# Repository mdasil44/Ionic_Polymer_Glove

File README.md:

# Ionic Polymer Glove

This repo contains the files used for testing and analyzing the performance of the sensorized glove using ionic polymer sensors.
The GUI is under sensorized-glove/Code/GUI/Matlab/IonicPolymerGloveGUI.mlapp

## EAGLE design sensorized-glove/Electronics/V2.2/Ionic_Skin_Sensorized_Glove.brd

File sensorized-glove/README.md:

# README #

### Summary ###

This repository contains all the relevant files for the ionic polymer sensorized glove project.

### Installation ###

- Matlab (See information engineering IT website)
- USB to bluetooth driver (See README.md in Code/Firmware/Bluetooth USB driver directory

### Contact ###

Developed by Andrew Cullen [acullen5@uwo.ca]

Supervised by Aaron Price [aaron.price@uwo.ca] and Ana Luisa Trejos [atrejos@uwo.ca]

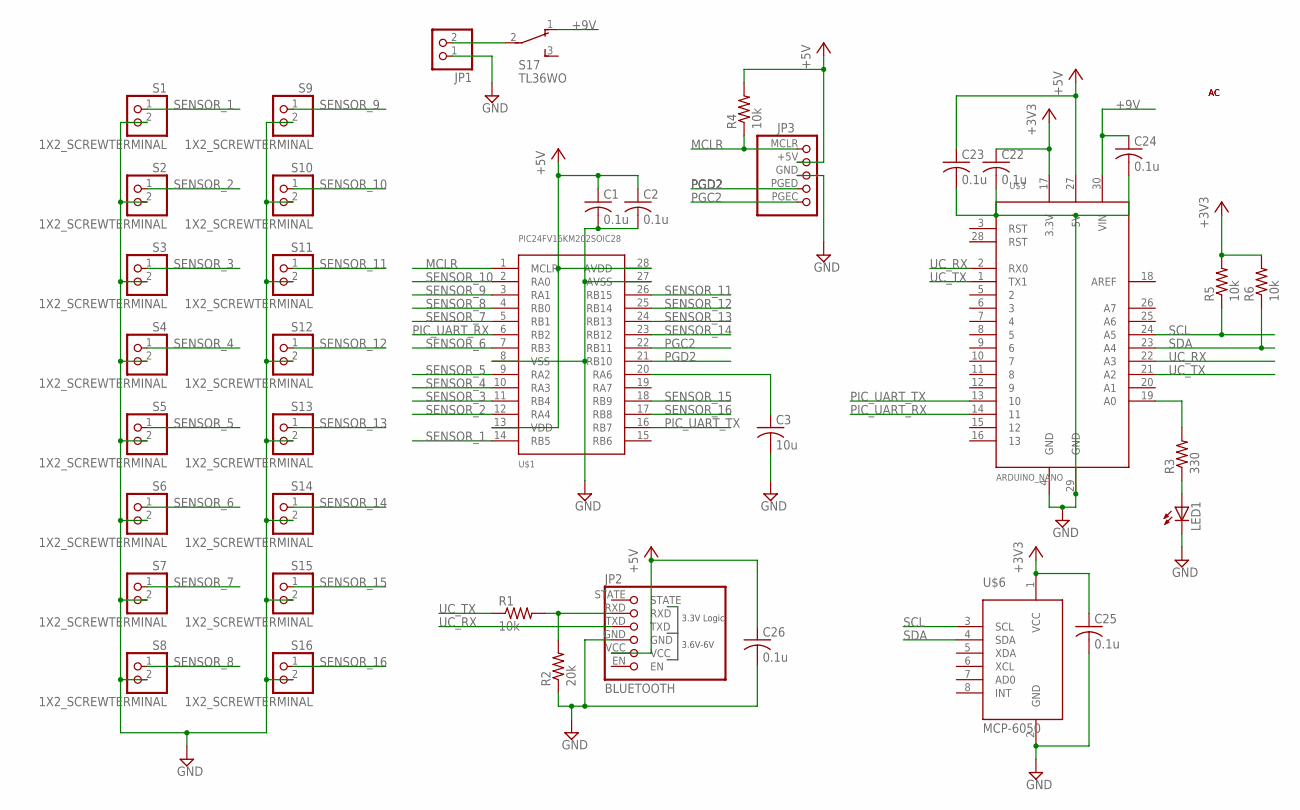
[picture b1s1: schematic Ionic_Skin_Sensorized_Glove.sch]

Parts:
C1, C2, C22, C23, C24, C25, C26: 0.1u; C0805
C3: 10u; C0805
JP1: PINHD-1X2; 1X02
JP2: BLUETOOTH; HC-06
JP3: PICKIT/90
LED1: LEDCHIPLED_0805; CHIPLED_0805
R1, R4, R5, R6: 10k; R0805
R2: 20k; R0805
R3: 330; R0805
S1, S2, S3, S4, S5, S6, S7, S8, S9, S10, S11, S12, S13, S14, S15, S16: 1X2_SCREWTERMINAL; 1X2-2.54MM
S17: TL36WO; TL3XWO
U$1: PIC24FV16KM202SOIC28; SOIC28
U$3: ARDUINO_NANO
U$6: MCP-6050; MCP-6050_BREAKOUT
U$7: AC_TOP
U$8: AC_BOTTOM

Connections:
+3V3: C22.1, C25.1, R5.2, R6.2, U$3.17 (3.3V), U$6.1 (VCC)
+5V: C1.1, C2.1, C23.1, C26.1, JP2.VCC, JP3.+5V (2), R4.2, U$1.13 (VDD), U$1.28 (AVDD), U$3.27 (5V)
+9V: C24.1, S17.1 (O), U$3.30 (VIN)
GND: C1.2, C2.2, C3.2, C22.2, C23.2, C24.2, C25.2, C26.2, JP1.1, JP2.GND, JP3.GND (3), LED1.C, R2.1, S1.2, S2.2, S3.2, S4.2, S5.2, S6.2, S7.2, S8.2, S9.2, S10.2, S11.2, S12.2, S13.2, S14.2, S15.2, S16.2, U$1.8 (VSS), U$1.27 (AVSS), U$3.4 (GND), U$3.29 (GND), U$6.2 (GND)
MCLR: JP3.MCLR (1), R4.1, U$1.1 (MCLR)
unnamed: C3.1, U$1.20 (RA6)
unnamed: JP1.2, S17.2
unnamed: LED1.A, R3.1
unnamed: R3.2, U$3.19 (A0)
unnamed: JP2.RXD, R1.2, R2.2
PGC2: JP3.PGEC (5), U$1.22 (RB11)
PGD2: JP3.PGED (4), U$1.21 (RB10)
PIC_UART_RX: U$1.6 (RB2), U$3.14 (11)
PIC_UART_TX: U$1.16 (RB7), U$3.13 (10)
SCL: R5.1, U$3.24 (A5), U$6.3 (SCL)
SDA: R6.1, U$3.23 (A4), U$6.4 (SDA)
SENSOR_1: S1.1, U$1.14 (RB5)
SENSOR_2: S2.1, U$1.12 (RA4)
SENSOR_3: S3.1, U$1.11 (RB4)
SENSOR_4: S4.1, U$1.10 (RA3)
SENSOR_5: S5.1, U$1.9 (RA2)
SENSOR_6: S6.1, U$1.7 (RB3)
SENSOR_7: S7.1, U$1.5 (RB1)
SENSOR_8: S8.1, U$1.4 (RB0)
SENSOR_9: S9.1, U$1.3 (RA1)
SENSOR_10: S10.1, U$1.2 (RA0)
SENSOR_11: S11.1, U$1.26 (RB15)
SENSOR_12: S12.1, U$1.25 (RB14)
SENSOR_13: S13.1, U$1.24 (RB13)
SENSOR_14: S14.1, U$1.23 (RB12)
SENSOR_15: S15.1, U$1.18 (RB9)
SENSOR_16: S16.1, U$1.17 (RB8)
UC_RX: JP2.TXD, U$3.2 (RX0), U$3.22 (A3)
UC_TX: R1.1, U$3.1 (TX1), U$3.21 (A2)

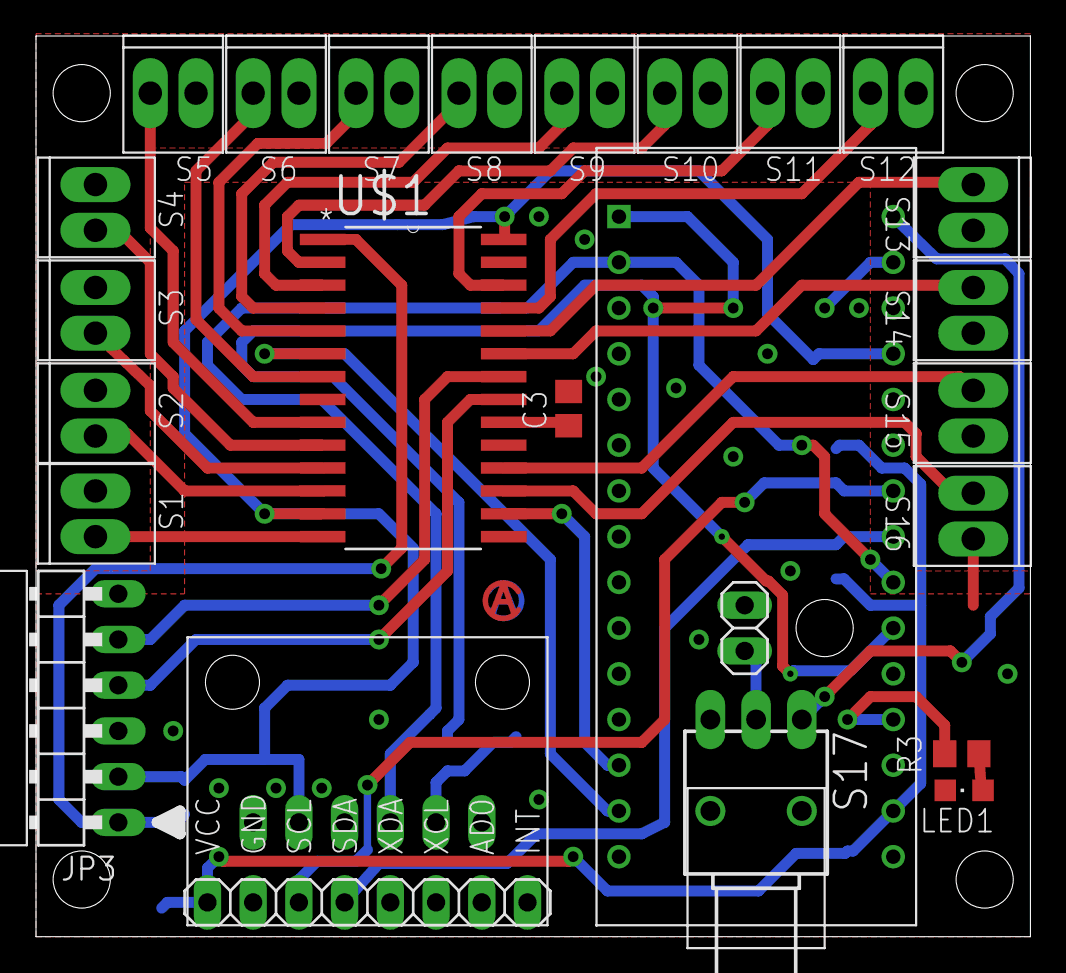
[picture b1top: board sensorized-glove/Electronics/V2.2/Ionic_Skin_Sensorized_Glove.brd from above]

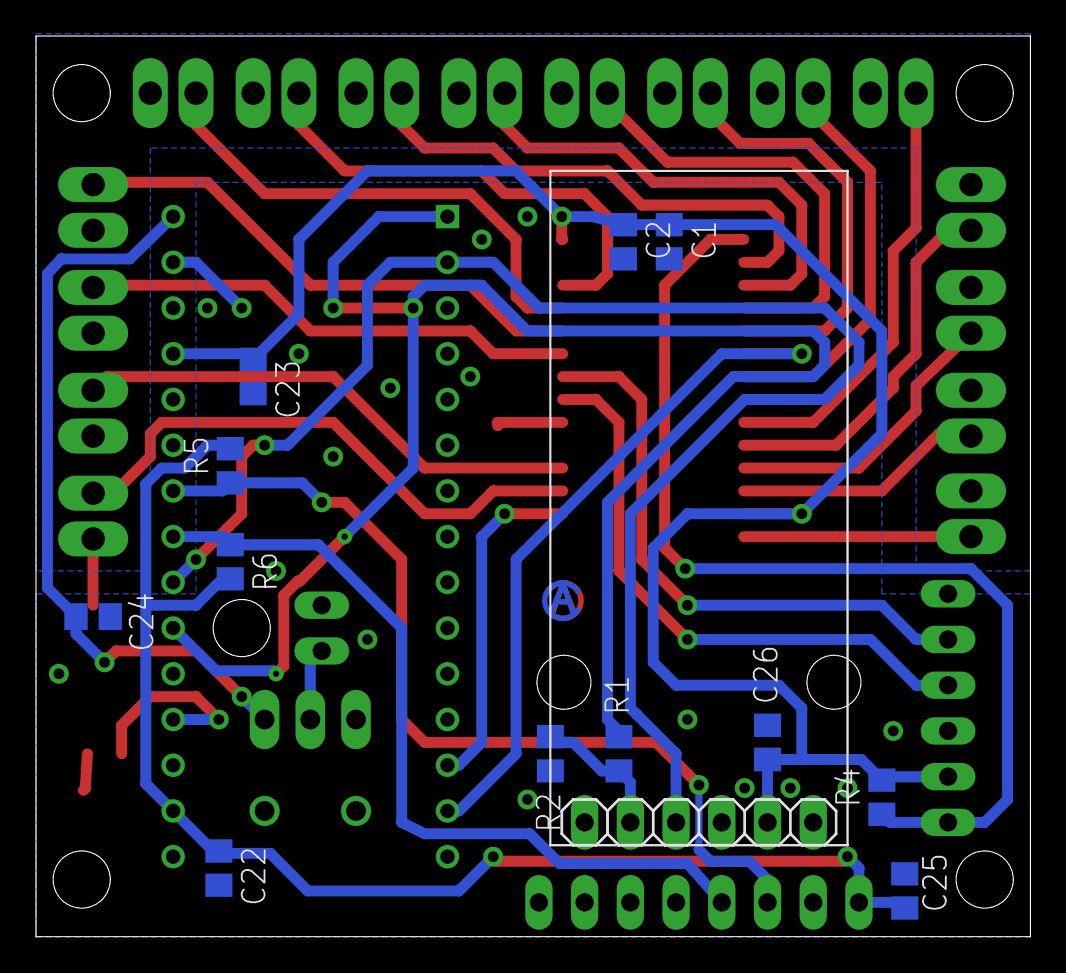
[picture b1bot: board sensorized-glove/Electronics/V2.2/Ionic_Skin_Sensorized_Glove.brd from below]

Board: 2 copper layers, 55.2 x 50.0 mm, 40 parts (13 on the bottom side), 34 nets.

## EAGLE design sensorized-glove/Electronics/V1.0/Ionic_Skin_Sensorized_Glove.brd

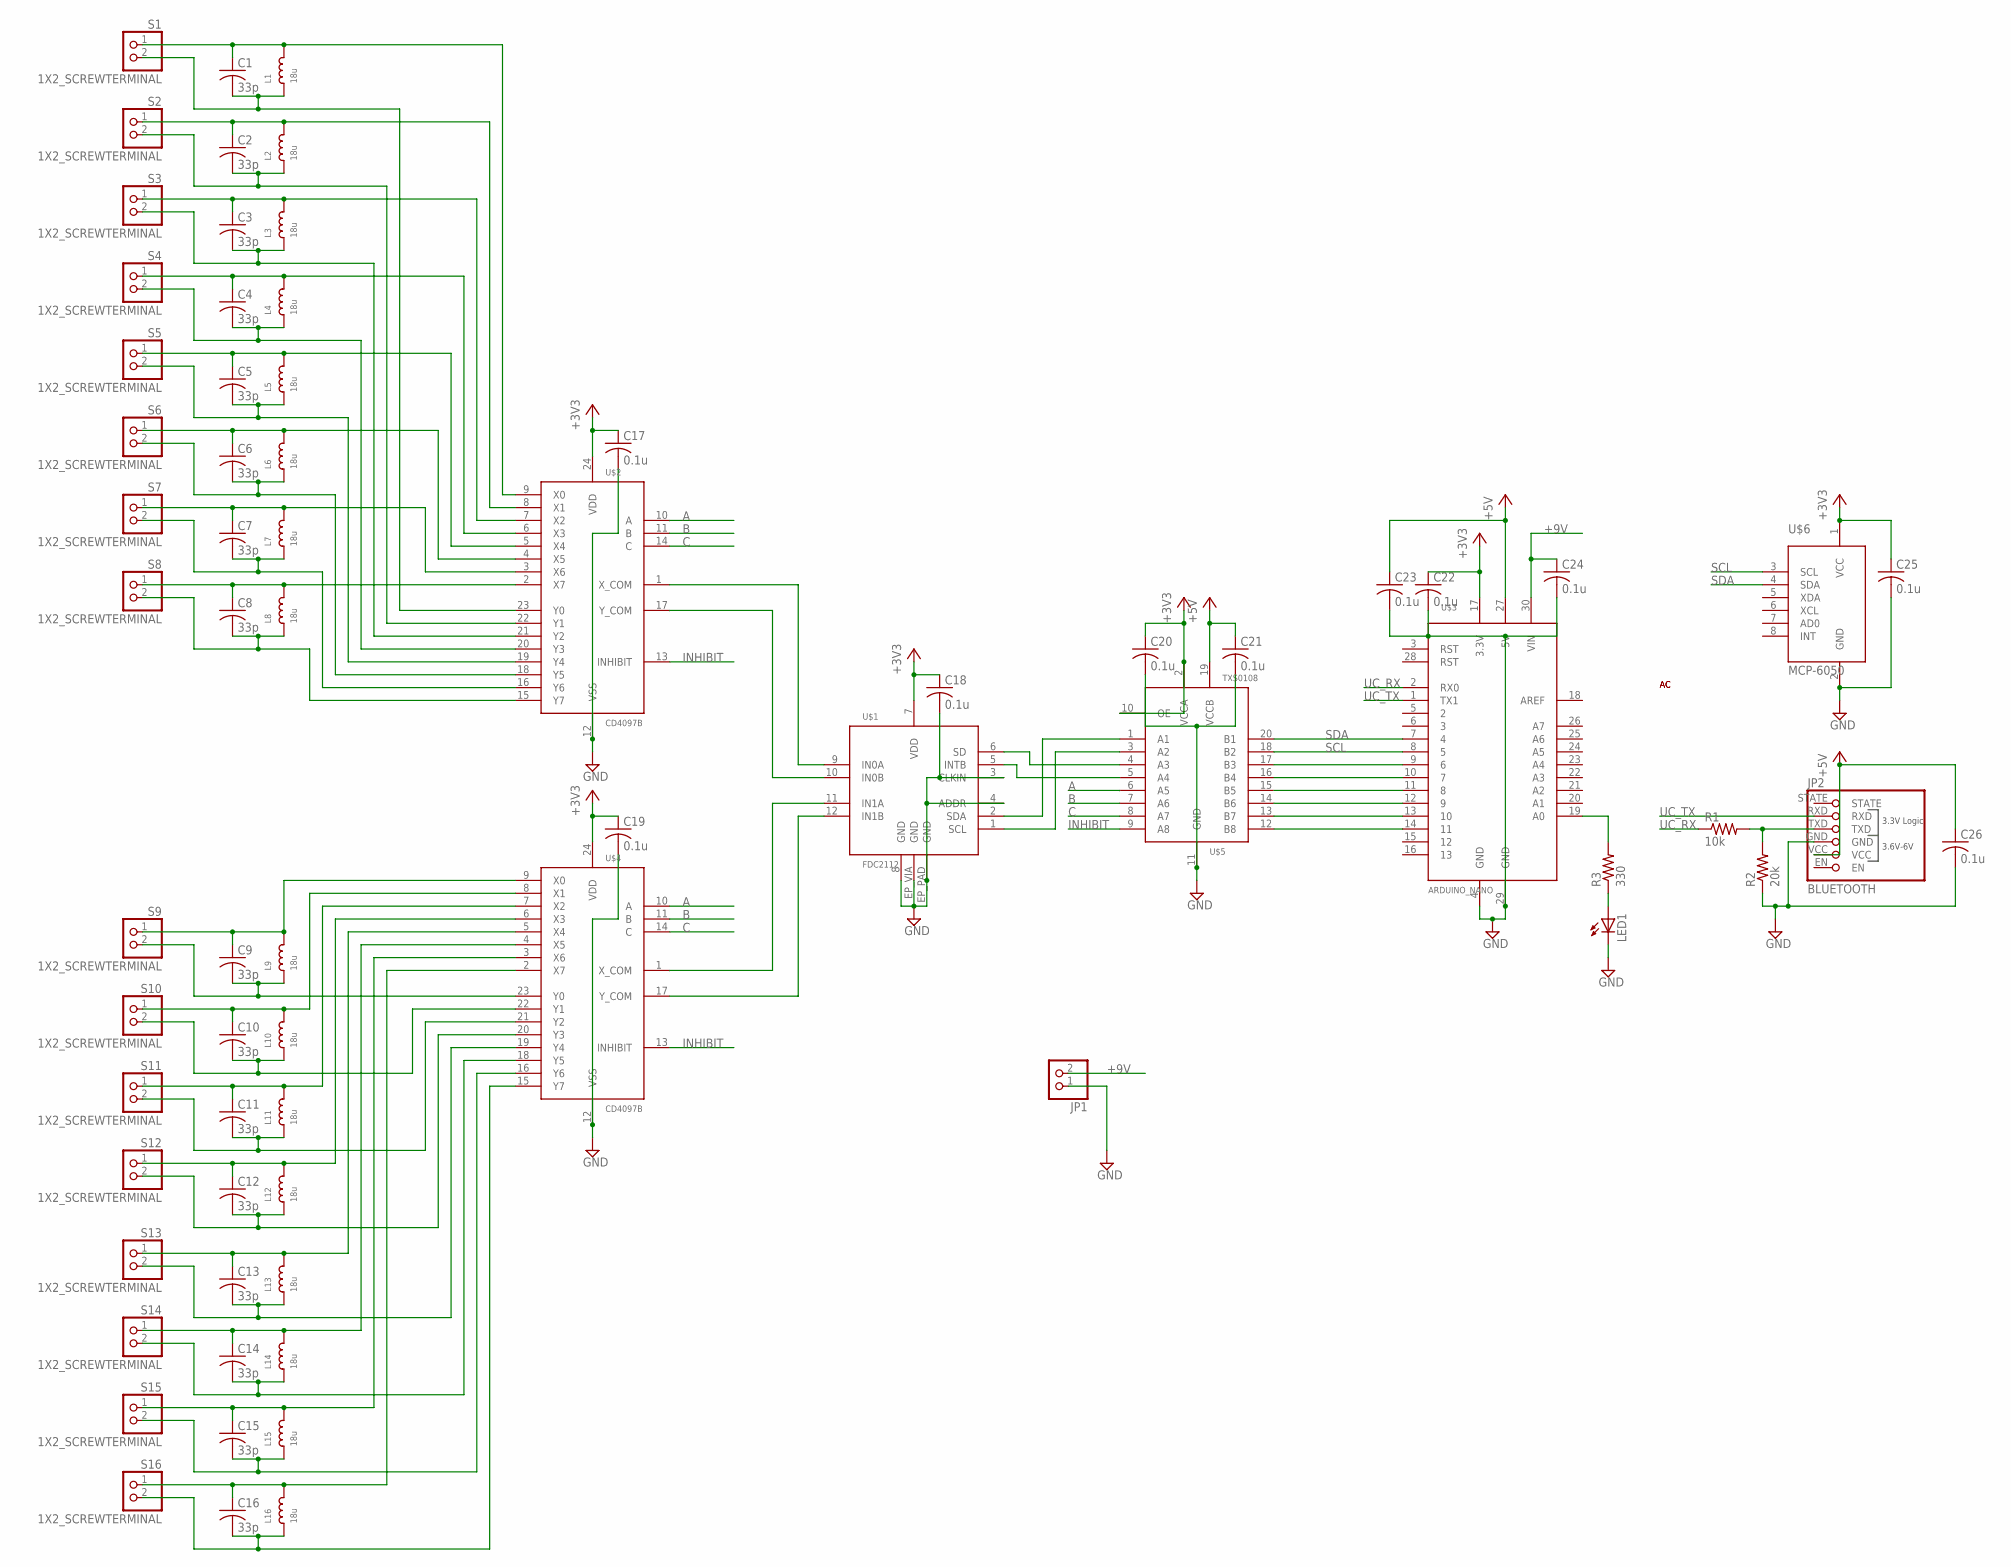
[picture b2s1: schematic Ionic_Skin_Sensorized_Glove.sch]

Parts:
C1, C2, C3, C4, C5, C6, C7, C8, C9, C10, C11, C12, C13, C14, C15, C16: 33p; C0805
C17, C18, C19, C20, C21, C22, C23, C24, C25, C26: 0.1u; C0805
JP1: PINHD-1X2; 1X02
JP2: BLUETOOTH; HC-06
L1, L2, L3, L4, L5, L6, L7, L8, L9, L10, L11, L12, L13, L14, L15, L16: 18u; _0805MP
LED1: LEDCHIPLED_0805; CHIPLED_0805
R1: 10k; R0805
R2: 20k; R0805
R3: 330; R0805
S1, S2, S3, S4, S5, S6, S7, S8, S9, S10, S11, S12, S13, S14, S15, S16: 1X2_SCREWTERMINAL; 1X2-2.54MM
U$1: FDC2112; WSON-12
U$2, U$4: CD4097B; TSSOP-24
U$3: ARDUINO_NANO
U$5: TXS0108; TSSOP-20
U$6: MCP-6050; MCP-6050_BREAKOUT
U$7: AC_TOP
U$8: AC_BOTTOM

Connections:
+3V3: C17.1, C18.1, C19.1, C20.1, C22.1, C25.1, U$1.7 (VDD), U$2.24 (VDD), U$3.17 (3.3V), U$4.24 (VDD), U$5.2 (VCCA), U$5.10 (OE), U$6.1 (VCC)
+5V: C21.1, C23.1, C26.1, JP2.VCC, U$3.27 (5V), U$5.19 (VCCB)
+9V: C24.1, JP1.2, U$3.30 (VIN)
A: U$2.10 (A), U$4.10 (A), U$5.6 (A5)
B: U$2.11 (B), U$4.11 (B), U$5.7 (A6)
C: U$2.14 (C), U$4.14 (C), U$5.8 (A7)
GND: C17.2, C18.2, C19.2, C20.2, C21.2, C22.2, C23.2, C24.2, C25.2, C26.2, JP1.1, JP2.GND, LED1.C, R2.1, U$1.3 (CLKIN), U$1.4 (ADDR), U$1.8 (GND), U$1.EP_PAD (GND), U$1.EP_VIA (GND), U$2.12 (VSS), U$3.4 (GND), U$3.29 (GND), U$4.12 (VSS), U$5.11 (GND), U$6.2 (GND)
INHIBIT: U$2.13 (INHIBIT), U$4.13 (INHIBIT), U$5.9 (A8)
unnamed: U$1.10 (IN0B), U$2.17 (Y_COM)
unnamed: U$1.9 (IN0A), U$2.1 (X_COM)
unnamed: U$1.11 (IN1A), U$4.1 (X_COM)
unnamed: U$1.12 (IN1B), U$4.17 (Y_COM)
unnamed: U$1.2 (SDA), U$5.1 (A1)
unnamed: U$1.1 (SCL), U$5.3 (A2)
unnamed: U$1.6 (SD), U$5.4 (A3)
unnamed: U$1.5 (INTB), U$5.5 (A4)
unnamed: LED1.A, R3.1
unnamed: R3.2, U$3.19 (A0)
unnamed: U$3.9 (6), U$5.17 (B3)
unnamed: U$3.10 (7), U$5.16 (B4)
unnamed: U$3.11 (8), U$5.15 (B5)
unnamed: U$3.12 (9), U$5.14 (B6)
unnamed: U$3.13 (10), U$5.13 (B7)
unnamed: U$3.14 (11), U$5.12 (B8)
unnamed: C1.2, L1.1, S1.2, U$2.23 (Y0)
unnamed: C1.1, L1.2, S1.1, U$2.9 (X0)
unnamed: C2.2, L2.1, S2.2, U$2.22 (Y1)
unnamed: C2.1, L2.2, S2.1, U$2.8 (X1)
unnamed: C3.2, L3.1, S3.2, U$2.21 (Y2)
unnamed: C3.1, L3.2, S3.1, U$2.7 (X2)
unnamed: C4.2, L4.1, S4.2, U$2.20 (Y3)
unnamed: C4.1, L4.2, S4.1, U$2.6 (X3)
unnamed: C5.2, L5.1, S5.2, U$2.19 (Y4)
unnamed: C5.1, L5.2, S5.1, U$2.5 (X4)
unnamed: C6.2, L6.1, S6.2, U$2.18 (Y5)
unnamed: C6.1, L6.2, S6.1, U$2.4 (X5)
unnamed: C7.2, L7.1, S7.2, U$2.16 (Y6)
unnamed: C8.2, L8.1, S8.2, U$2.15 (Y7)
unnamed: C8.1, L8.2, S8.1, U$2.2 (X7)
unnamed: C7.1, L7.2, S7.1, U$2.3 (X6)
unnamed: C9.2, L9.1, S9.2, U$4.23 (Y0)
unnamed: C9.1, L9.2, S9.1, U$4.9 (X0)
unnamed: C10.2, L10.1, S10.2, U$4.22 (Y1)
unnamed: C10.1, L10.2, S10.1, U$4.8 (X1)
unnamed: C11.2, L11.1, S11.2, U$4.21 (Y2)
unnamed: C11.1, L11.2, S11.1, U$4.7 (X2)
unnamed: C12.2, L12.1, S12.2, U$4.20 (Y3)
unnamed: C12.1, L12.2, S12.1, U$4.6 (X3)
unnamed: C13.2, L13.1, S13.2, U$4.19 (Y4)
unnamed: C13.1, L13.2, S13.1, U$4.5 (X4)
unnamed: C14.2, L14.1, S14.2, U$4.18 (Y5)
unnamed: C14.1, L14.2, S14.1, U$4.4 (X5)
unnamed: C15.2, L15.1, S15.2, U$4.16 (Y6)
unnamed: C15.1, L15.2, S15.1, U$4.3 (X6)
unnamed: C16.2, L16.1, S16.2, U$4.15 (Y7)
unnamed: C16.1, L16.2, S16.1, U$4.2 (X7)
unnamed: JP2.TXD, R1.2, R2.2
SCL: U$3.8 (5), U$5.18 (B2), U$6.3 (SCL)
SDA: U$3.7 (4), U$5.20 (B1), U$6.4 (SDA)
UC_RX: R1.1, U$3.2 (RX0)
UC_TX: JP2.RXD, U$3.1 (TX1)

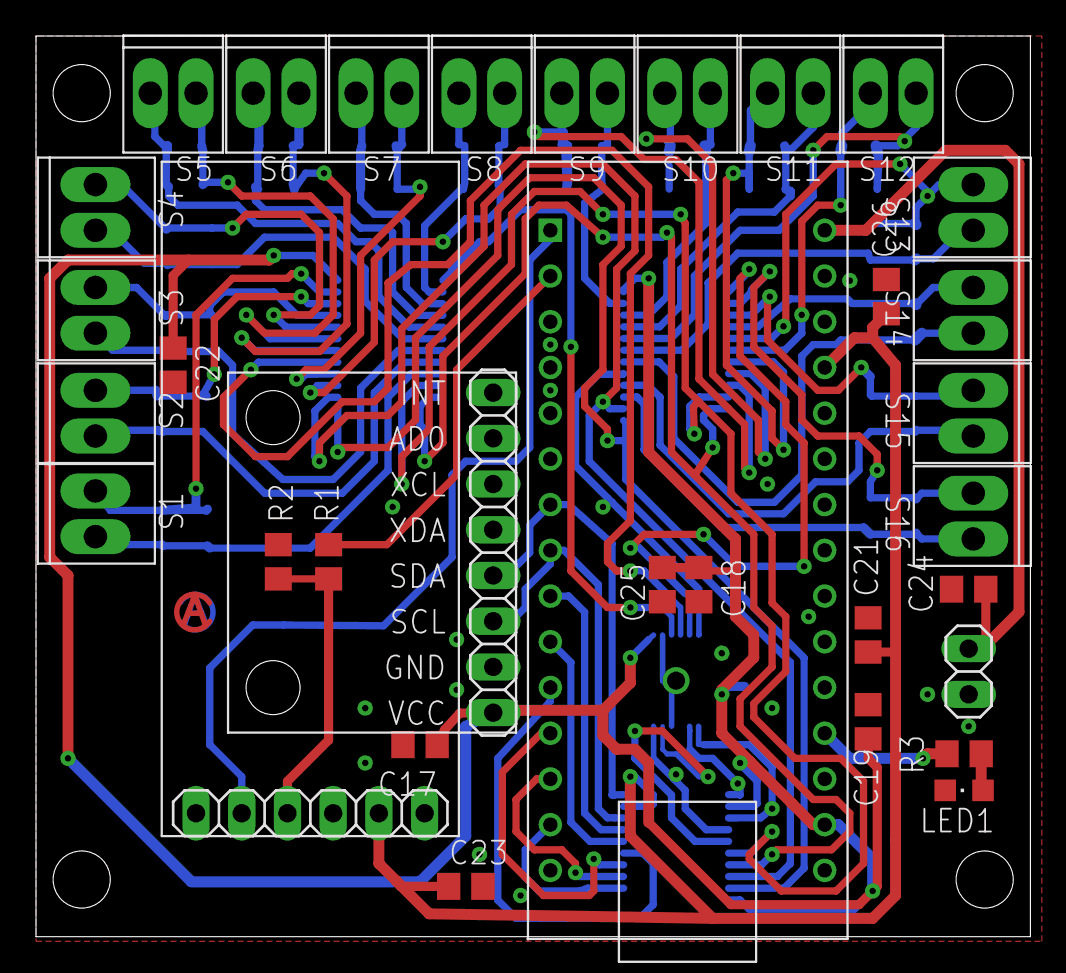
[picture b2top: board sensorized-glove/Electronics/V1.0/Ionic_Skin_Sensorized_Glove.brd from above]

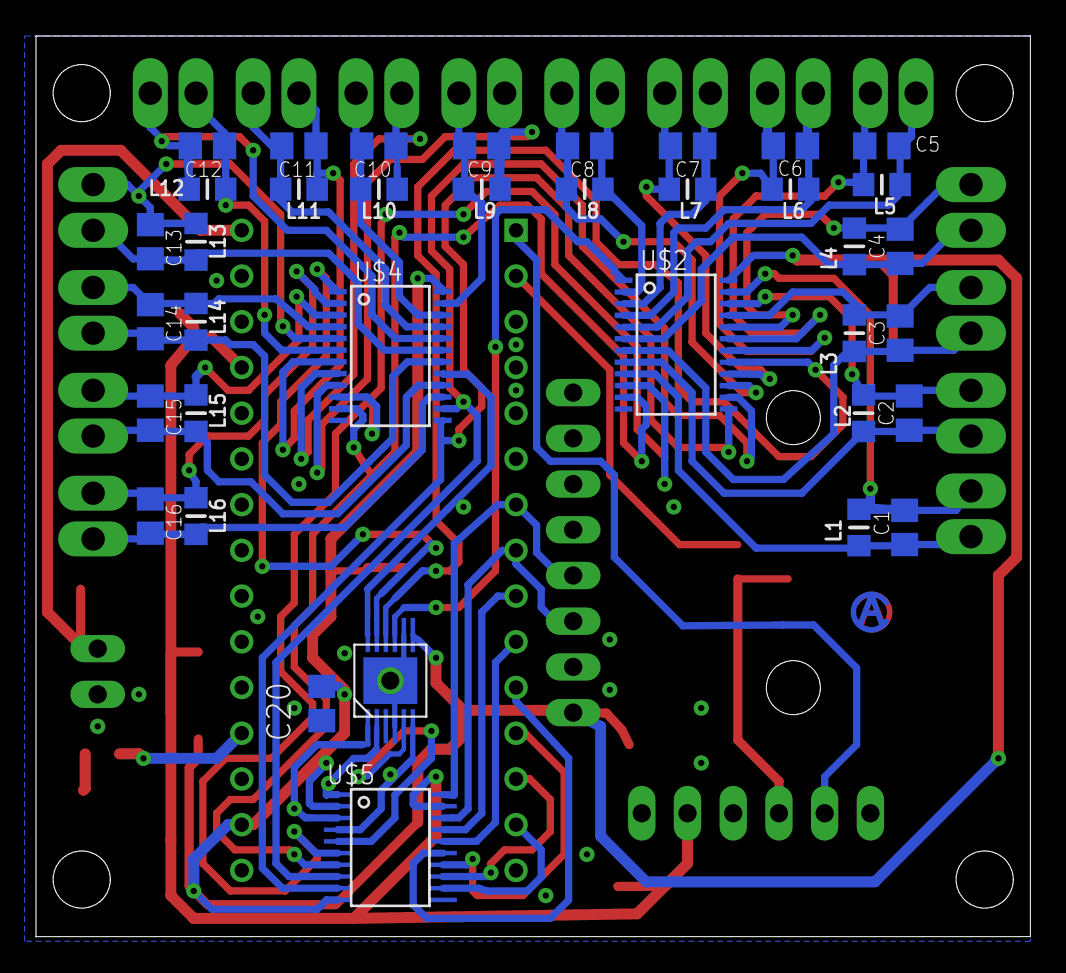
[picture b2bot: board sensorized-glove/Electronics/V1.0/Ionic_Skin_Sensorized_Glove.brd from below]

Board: 2 copper layers, 55.2 x 50.0 mm, 72 parts (37 on the bottom side), 61 nets.

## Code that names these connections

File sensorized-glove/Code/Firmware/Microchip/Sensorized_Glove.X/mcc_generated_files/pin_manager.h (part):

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*/
/**
  @Summary
    Sets the GPIO pin, RA0, high using LATA0.

  @Description
    Sets the GPIO pin, RA0, high using LATA0.

  @Preconditions
    The RA0 must be set to an output.
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#define Sensor_9_SetHigh()          _LATA0 = 1
/**
  @Summary
    Sets the GPIO pin, RA0, low using LATA0.

  @Description
    Sets the GPIO pin, RA0, low using LATA0.

  @Preconditions
    The RA0 must be set to an output.
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#define Sensor_9_SetLow()           _LATA0 = 0
/**
  @Summary
    Toggles the GPIO pin, RA0, using LATA0.

  @Description
    Toggles the GPIO pin, RA0, using LATA0.

  @Preconditions
    The RA0 must be set to an output.
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#define Sensor_9_Toggle()           _LATA0 ^= 1
/**
  @Summary
    Reads the value of the GPIO pin, RA0.

  @Description
    Reads the value of the GPIO pin, RA0.

  @Preconditions
    None.
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    </code>

*/
#define Sensor_9_GetValue()         _RA0
/**
  @Summary
    Configures the GPIO pin, RA0, as an input.

  @Description
    Configures the GPIO pin, RA0, as an input.

  @Preconditions
    None.
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#define Sensor_9_SetDigitalInput()  _TRISA0 = 1
/**
  @Summary
    Configures the GPIO pin, RA0, as an output.

  @Description
    Configures the GPIO pin, RA0, as an output.

  @Preconditions
    None.
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#define Sensor_9_SetDigitalOutput() _TRISA0 = 0
/**
  @Summary
    Sets the GPIO pin, RA1, high using LATA1.

  @Description
    Sets the GPIO pin, RA1, high using LATA1.

  @Preconditions
    The RA1 must be set to an output.
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#define Sensor_8_SetHigh()          _LATA1 = 1
/**
  @Summary
    Sets the GPIO pin, RA1, low using LATA1.

  @Description
    Sets the GPIO pin, RA1, low using LATA1.

  @Preconditions
    The RA1 must be set to an output.
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#define Sensor_8_SetLow()           _LATA1 = 0
/**
  @Summary
    Toggles the GPIO pin, RA1, using LATA1.

  @Description
    Toggles the GPIO pin, RA1, using LATA1.

  @Preconditions
    The RA1 must be set to an output.
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#define Sensor_8_Toggle()           _LATA1 ^= 1
/**
  @Summary
    Reads the value of the GPIO pin, RA1.

  @Description
    Reads the value of the GPIO pin, RA1.

  @Preconditions
    None.
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    </code>

*/
#define Sensor_8_GetValue()         _RA1
/**
  @Summary
    Configures the GPIO pin, RA1, as an input.

  @Description
    Configures the GPIO pin, RA1, as an input.

  @Preconditions
    None.
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#define Sensor_8_SetDigitalInput()  _TRISA1 = 1
/**
  @Summary
    Configures the GPIO pin, RA1, as an output.

  @Description
    Configures the GPIO pin, RA1, as an output.

  @Preconditions
    None.
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#define Sensor_8_SetDigitalOutput() _TRISA1 = 0
/**
  @Summary
    Sets the GPIO pin, RA2, high using LATA2.

  @Description
    Sets the GPIO pin, RA2, high using LATA2.

  @Preconditions
    The RA2 must be set to an output.
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#define Sensor_4_SetHigh()          _LATA2 = 1
/**
  @Summary
    Sets the GPIO pin, RA2, low using LATA2.

  @Description
    Sets the GPIO pin, RA2, low using LATA2.

  @Preconditions
    The RA2 must be set to an output.
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#define Sensor_4_SetLow()           _LATA2 = 0
/**
  @Summary
    Toggles the GPIO pin, RA2, using LATA2.

  @Description
    Toggles the GPIO pin, RA2, using LATA2.

  @Preconditions
    The RA2 must be set to an output.
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#define Sensor_4_Toggle()           _LATA2 ^= 1
/**
  @Summary
    Reads the value of the GPIO pin, RA2.

  @Description
    Reads the value of the GPIO pin, RA2.

  @Preconditions
    None.
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    </code>

*/
#define Sensor_4_GetValue()         _RA2
/**
  @Summary
    Configures the GPIO pin, RA2, as an input.

  @Description
    Configures the GPIO pin, RA2, as an input.

  @Preconditions
    None.
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#define Sensor_4_SetDigitalInput()  _TRISA2 = 1
/**
  @Summary
    Configures the GPIO pin, RA2, as an output.

  @Description
    Configures the GPIO pin, RA2, as an output.

  @Preconditions
    None.
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#define Sensor_4_SetDigitalOutput() _TRISA2 = 0
/**
  @Summary
    Sets the GPIO pin, RA3, high using LATA3.

  @Description
    Sets the GPIO pin, RA3, high using LATA3.

  @Preconditions
    The RA3 must be set to an output.
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#define Sensor_3_SetHigh()          _LATA3 = 1
/**
  @Summary
    Sets the GPIO pin, RA3, low using LATA3.

  @Description
    Sets the GPIO pin, RA3, low using LATA3.

  @Preconditions
    The RA3 must be set to an output.
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#define Sensor_3_SetLow()           _LATA3 = 0
/**
  @Summary
    Toggles the GPIO pin, RA3, using LATA3.

  @Description
    Toggles the GPIO pin, RA3, using LATA3.

  @Preconditions
    The RA3 must be set to an output.
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#define Sensor_3_Toggle()           _LATA3 ^= 1
/**
  @Summary
    Reads the value of the GPIO pin, RA3.

  @Description
    Reads the value of the GPIO pin, RA3.

  @Preconditions
    None.
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    </code>

*/
#define Sensor_3_GetValue()         _RA3
/**
  @Summary
    Configures the GPIO pin, RA3, as an input.

  @Description
    Configures the GPIO pin, RA3, as an input.

  @Preconditions
    None.
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#define Sensor_3_SetDigitalInput()  _TRISA3 = 1
/**
  @Summary
    Configures the GPIO pin, RA3, as an output.

  @Description
    Configures the GPIO pin, RA3, as an output.

  @Preconditions
    None.
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#define Sensor_3_SetDigitalOutput() _TRISA3 = 0
/**
  @Summary
    Sets the GPIO pin, RA4, high using LATA4.

  @Description
    Sets the GPIO pin, RA4, high using LATA4.

  @Preconditions
    The RA4 must be set to an output.
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#define Sensor_1_SetHigh()          _LATA4 = 1
/**
  @Summary
    Sets the GPIO pin, RA4, low using LATA4.

  @Description
    Sets the GPIO pin, RA4, low using LATA4.

  @Preconditions
    The RA4 must be set to an output.
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#define Sensor_1_SetLow()           _LATA4 = 0
/**
  @Summary
    Toggles the GPIO pin, RA4, using LATA4.

  @Description
    Toggles the GPIO pin, RA4, using LATA4.

  @Preconditions
    The RA4 must be set to an output.
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#define Sensor_1_Toggle()           _LATA4 ^= 1
/**
  @Summary
    Reads the value of the GPIO pin, RA4.

  @Description
    Reads the value of the GPIO pin, RA4.

  @Preconditions
    None.
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    </code>

*/
#define Sensor_1_GetValue()         _RA4
/**
  @Summary
    Configures the GPIO pin, RA4, as an input.

  @Description
    Configures the GPIO pin, RA4, as an input.

  @Preconditions
    None.
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#define Sensor_1_SetDigitalInput()  _TRISA4 = 1
/**
  @Summary
    Configures the GPIO pin, RA4, as an output.

  @Description
    Configures the GPIO pin, RA4, as an output.

  @Preconditions
    None.
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#define Sensor_1_SetDigitalOutput() _TRISA4 = 0
/**
  @Summary
    Sets the GPIO pin, RB0, high using LATB0.

  @Description
    Sets the GPIO pin, RB0, high using LATB0.

  @Preconditions
    The RB0 must be set to an output.
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#define Sensor_7_SetHigh()          _LATB0 = 1
/**
  @Summary
    Sets the GPIO pin, RB0, low using LATB0.

  @Description
    Sets the GPIO pin, RB0, low using LATB0.

  @Preconditions
    The RB0 must be set to an output.
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#define Sensor_7_SetLow()           _LATB0 = 0
/**
  @Summary
    Toggles the GPIO pin, RB0, using LATB0.

  @Description
    Toggles the GPIO pin, RB0, using LATB0.

  @Preconditions
    The RB0 must be set to an output.
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#define Sensor_7_Toggle()           _LATB0 ^= 1
/**
  @Summary
    Reads the value of the GPIO pin, RB0.

  @Description
    Reads the value of the GPIO pin, RB0.

  @Preconditions
    None.
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    </code>

*/
#define Sensor_7_GetValue()         _RB0
/**
  @Summary
    Configures the GPIO pin, RB0, as an input.

  @Description
    Configures the GPIO pin, RB0, as an input.

  @Preconditions
    None.
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#define Sensor_7_SetDigitalInput()  _TRISB0 = 1
/**
  @Summary
    Configures the GPIO pin, RB0, as an output.

  @Description
    Configures the GPIO pin, RB0, as an output.

  @Preconditions
    None.
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#define Sensor_7_SetDigitalOutput() _TRISB0 = 0
/**
  @Summary
    Sets the GPIO pin, RB1, high using LATB1.

  @Description
    Sets the GPIO pin, RB1, high using LATB1.

  @Preconditions
    The RB1 must be set to an output.
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#define Sensor_6_SetHigh()          _LATB1 = 1
/**
  @Summary
    Sets the GPIO pin, RB1, low using LATB1.

  @Description
    Sets the GPIO pin, RB1, low using LATB1.

  @Preconditions
    The RB1 must be set to an output.
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#define Sensor_6_SetLow()           _LATB1 = 0
/**
  @Summary
    Toggles the GPIO pin, RB1, using LATB1.

  @Description
    Toggles the GPIO pin, RB1, using LATB1.

  @Preconditions
    The RB1 must be set to an output.
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#define Sensor_6_Toggle()           _LATB1 ^= 1
/**
  @Summary
    Reads the value of the GPIO pin, RB1.

  @Description
    Reads the value of the GPIO pin, RB1.

  @Preconditions
    None.
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    </code>

*/
#define Sensor_6_GetValue()         _RB1
/**
  @Summary
    Configures the GPIO pin, RB1, as an input.

  @Description
    Configures the GPIO pin, RB1, as an input.

  @Preconditions
    None.
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#define Sensor_6_SetDigitalInput()  _TRISB1 = 1
/**
  @Summary
    Configures the GPIO pin, RB1, as an output.

  @Description
    Configures the GPIO pin, RB1, as an output.

  @Preconditions
    None.
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#define Sensor_6_SetDigitalOutput() _TRISB1 = 0
/**
  @Summary
    Sets the GPIO pin, RB12, high using LATB12.
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
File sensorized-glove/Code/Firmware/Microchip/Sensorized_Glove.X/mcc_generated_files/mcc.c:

/**
  @Generated PIC24 / dsPIC33 / PIC32MM MCUs Source File

  @Company:
    Microchip Technology Inc.

  @File Name:
    mcc.c

  @Summary:
    This is the mcc.c file generated using PIC24 / dsPIC33 / PIC32MM MCUs

  @Description:
    This header file provides implementations for driver APIs for all modules selected in the GUI.
    Generation Information :
        Product Revision  :  PIC24 / dsPIC33 / PIC32MM MCUs - pic24-dspic-pic32mm : v1.35
        Device            :  PIC24FV16KM202
    The generated drivers are tested against the following:
        Compiler          :  XC16 1.31
        MPLAB             :  MPLAB X 3.60
*/

/*
    (c) 2016 Microchip Technology Inc. and its subsidiaries. You may use this
    software and any derivatives exclusively with Microchip products.

    THIS SOFTWARE IS SUPPLIED BY MICROCHIP "AS IS". NO WARRANTIES, WHETHER
    EXPRESS, IMPLIED OR STATUTORY, APPLY TO THIS SOFTWARE, INCLUDING ANY IMPLIED
    WARRANTIES OF NON-INFRINGEMENT, MERCHANTABILITY, AND FITNESS FOR A
    PARTICULAR PURPOSE, OR ITS INTERACTION WITH MICROCHIP PRODUCTS, COMBINATION
    WITH ANY OTHER PRODUCTS, OR USE IN ANY APPLICATION.

    IN NO EVENT WILL MICROCHIP BE LIABLE FOR ANY INDIRECT, SPECIAL, PUNITIVE,
    INCIDENTAL OR CONSEQUENTIAL LOSS, DAMAGE, COST OR EXPENSE OF ANY KIND
    WHATSOEVER RELATED TO THE SOFTWARE, HOWEVER CAUSED, EVEN IF MICROCHIP HAS
    BEEN ADVISED OF THE POSSIBILITY OR THE DAMAGES ARE FORESEEABLE. TO THE
    FULLEST EXTENT ALLOWED BY LAW, MICROCHIP'S TOTAL LIABILITY ON ALL CLAIMS IN
    ANY WAY RELATED TO THIS SOFTWARE WILL NOT EXCEED THE AMOUNT OF FEES, IF ANY,
    THAT YOU HAVE PAID DIRECTLY TO MICROCHIP FOR THIS SOFTWARE.

    MICROCHIP PROVIDES THIS SOFTWARE CONDITIONALLY UPON YOUR ACCEPTANCE OF THESE
    TERMS.
*/

// Configuration bits: selected in the GUI

// FBS
#pragma config BWRP = OFF    // Boot Segment Write Protect->Disabled
#pragma config BSS = OFF    // Boot segment Protect->No boot program flash segment

// FGS
#pragma config GWRP = OFF    // General Segment Write Protect->General segment may be written
#pragma config GCP = OFF    // General Segment Code Protect->No Protection

// FOSCSEL
#pragma config FNOSC = FRCDIV    // Oscillator Select->8MHz FRC oscillator With Postscaler (FRCDIV)
#pragma config SOSCSRC = ANA    // SOSC Source Type->Analog Mode for use with crystal
#pragma config LPRCSEL = HP    // LPRC Oscillator Power and Accuracy->High Power, High Accuracy Mode
#pragma config IESO = ON    // Internal External Switch Over bit->Internal External Switchover mode enabled (Two-speed Start-up enabled)

// FOSC
#pragma config POSCMOD = NONE    // Primary Oscillator Configuration bits->Primary oscillator disabled
#pragma config OSCIOFNC = IO    // CLKO Enable Configuration bit->Port I/O enabled (CLKO disabled)
#pragma config POSCFREQ = HS    // Primary Oscillator Frequency Range Configuration bits->Primary oscillator/external clock input frequency greater than 8MHz
#pragma config SOSCSEL = SOSCHP    // SOSC Power Selection Configuration bits->Secondary Oscillator configured for high-power operation
#pragma config FCKSM = CSDCMD    // Clock Switching and Monitor Selection->Both Clock Switching and Fail-safe Clock Monitor are disabled

// FWDT
#pragma config WDTPS = PS32768    // Watchdog Timer Postscale Select bits->1:32768
#pragma config FWPSA = PR128    // WDT Prescaler bit->WDT prescaler ratio of 1:128
#pragma config FWDTEN = SWON    // Watchdog Timer Enable bits->WDT controlled with the SWDTEN bit setting
#pragma config WINDIS = OFF    // Windowed Watchdog Timer Disable bit->Standard WDT selected(windowed WDT disabled)

// FPOR
#pragma config BOREN = BOR3    // Brown-out Reset Enable bits->Brown-out Reset enabled in hardware, SBOREN bit disabled
#pragma config RETCFG = OFF    // ->Retention regulator is not available
#pragma config PWRTEN = ON    // Power-up Timer Enable bit->PWRT enabled
#pragma config I2C1SEL = PRI    // Alternate I2C1 Pin Mapping bit->Use Default SCL1/SDA1 Pins For I2C1
#pragma config BORV = V18    // Brown-out Reset Voltage bits->Brown-out Reset set to lowest voltage (1.8V)
#pragma config MCLRE = ON    // MCLR Pin Enable bit->RA5 input pin disabled, MCLR pin enabled

// FICD
#pragma config ICS = PGx2    // ICD Pin Placement Select bits->EMUC/EMUD share PGC2/PGD2

#include "mcc.h"

void SYSTEM_Initialize(void)
{
    PIN_MANAGER_Initialize();
    OSCILLATOR_Initialize();
    INTERRUPT_Initialize();
    ADC1_Initialize();
    UART1_Initialize();
}

void OSCILLATOR_Initialize(void)
{
    // CF no clock failure; NOSC FRCDIV; SOSCEN disabled; SOSCDRV disabled; CLKLOCK unlocked; OSWEN Switch is Complete; 
    __builtin_write_OSCCONL((uint8_t) (0x0700 & 0x00FF));
    // RCDIV FRC/1; DOZE 1:8; DOZEN disabled; ROI disabled; 
    CLKDIV = 0x3000;
    // TUN Center frequency; 
    OSCTUN = 0x0000;
    // ROEN disabled; ROSEL disabled; RODIV Base clock value; ROSSLP disabled; 
    REFOCON = 0x0000;
}

/**
 End of File
*/

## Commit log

2018-07-19 Added Reference Sensor Test
    Test folder includes executable for reference sensor. REFERENCE SENSOR provides a directory to working C++ test code.
2018-07-19 Read Reference Sensor Files
2018-07-20 Added the edited original folders
2018-07-20 Added API files to read sensor
2018-07-20 Updated 2018-07-20
2018-07-24 Updated 2018-07-23
2018-07-24 Updated 2018-07-24: Added reference sensor plot
2018-07-25 Updated 2018-07-25: Working Ref. Sensor GUI
2018-07-25 Removed sensorized-glove folder
2018-07-25 Reuploading sensorized-glove folder
2018-07-26 Started calibration implementation
2018-07-27 Minor code updates to GUI
2018-07-31 Fixed up calibration code - not finished
2018-08-01 Working calibration update
2018-08-15 Started filter tests
2018-08-16 Added filter to capacitance values (smoothed)
2018-08-17 Started adding quadratic regression
2018-08-20 Limited Quadratic Regression
2018-08-21 For continued quadratic regression testing
2018-08-21 Filter Testing
2018-08-22 Added Test tab for calibration
2018-08-23 PIC + filter modification testing
2018-08-27 Reduced harmonic-induced noise

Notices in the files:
sensorized-glove/Code/Firmware/Microchip/Sensorized_Glove.X/mcc_generated_files/pin_manager.h:
Copyright (c) 2013 - 2015 released Microchip Technology Inc.  All rights reserved.
parts and their libraries:
microbuilder: This work is placed in the public domain, and may be freely used for commercial and non-commercial work with the following conditions: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
